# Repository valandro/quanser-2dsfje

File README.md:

# quanser-2dsfje

## Limit sensors schematic

## Authors

- Lucas Valandro (@valandro)
- Lucas Tansini (@lucastansini)
- Gustavo Francisco (@guga581)

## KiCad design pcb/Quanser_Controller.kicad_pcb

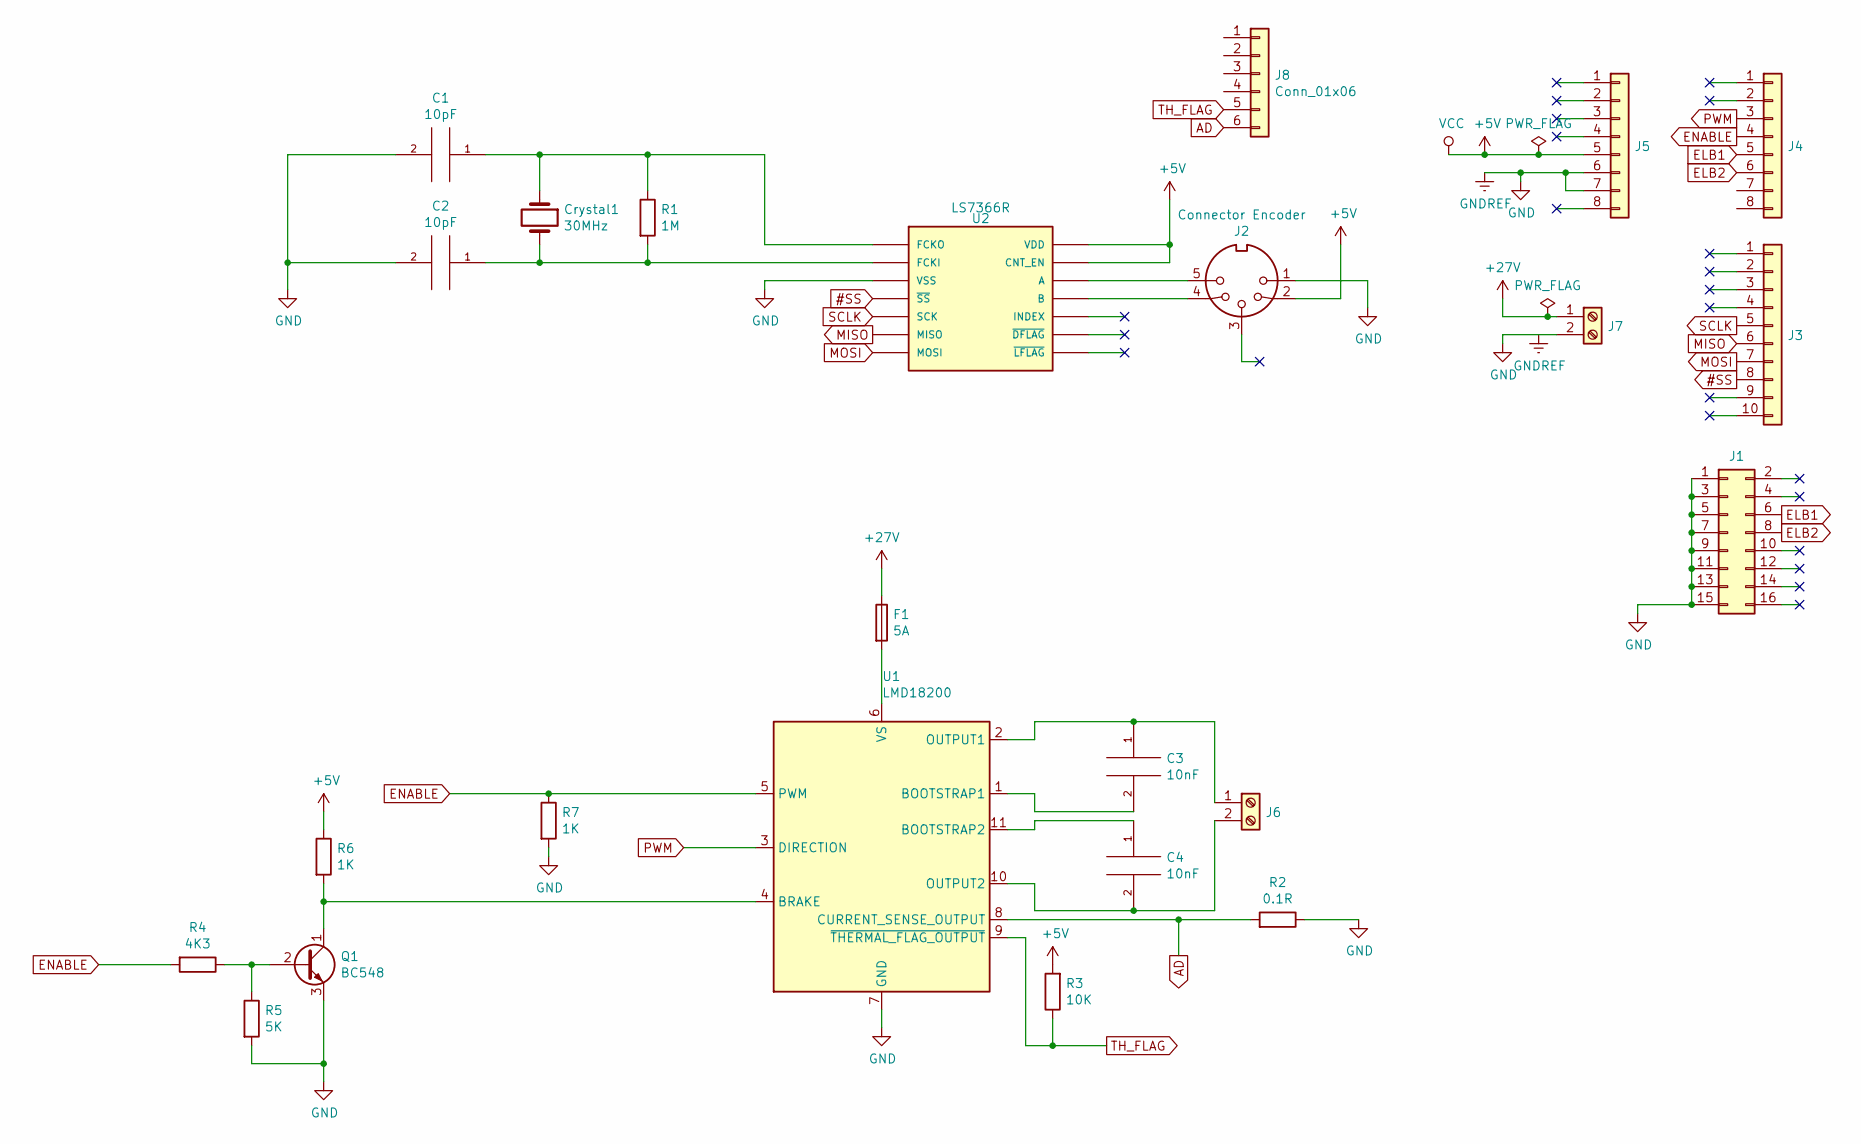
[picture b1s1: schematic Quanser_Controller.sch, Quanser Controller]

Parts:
C1, C2: 10pF; C_Disc_D3.0mm_W2.0mm_P2.50mm
C3, C4: 10nF; C_Disc_D3.0mm_W2.0mm_P2.50mm
Crystal1: 30MHz; Crystal_HC52-6mm_Vertical
F1: 5A; Fuseholder_Cylinder-5x20mm_Schurter_0031_8201_Horizontal_Op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
J1: Conn_02x08; PinHeader_2x08_P2.00mm_Vertical
J2: Connector Encoder; PinHeader_1x05_P2.54mm_Vertical
J3: Conn_01x10; PinHeader_1x10_P2.00mm_Vertical
J4, J5: Conn_01x08; PinHeader_1x08_P2.00mm_Vertical
J6, J7: Screw_Terminal_01x02; TerminalBlock_Altech_AK300-2_P5.00mm
J8: Conn_01x06; PinHeader_1x06_P2.00mm_Vertical
Q1: BC548; TO-92_Inline
R1: 1M; R_Axial_DIN0204_L3.6mm_D1.6mm_P5.08mm_Horizontal
R2: 0.1R; R_Axial_DIN0204_L3.6mm_D1.6mm_P5.08mm_Horizontal
R3: 10K; R_Axial_DIN0204_L3.6mm_D1.6mm_P5.08mm_Horizontal
R4: 4K3; R_Axial_DIN0204_L3.6mm_D1.6mm_P5.08mm_Horizontal
R5: 5K; R_Axial_DIN0204_L3.6mm_D1.6mm_P5.08mm_Horizontal
R6, R7: 1K; R_Axial_DIN0204_L3.6mm_D1.6mm_P5.08mm_Horizontal
U1: LMD18200; TO-220-11_P3.4x5.08mm_StaggerOdd_Lead4.85mm_Vertical
U2: LS7366R; DIP-14_W7.62mm

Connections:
#SS: J3.8, U2.4 (~SS~)
+5V: J2.2, J5.5, R3.2, R6.1, U2.13 (CNT_EN), U2.14 (VDD)
+28V: F1.1, J7.1
AD: J8.6, R2.2, U1.8 (CURRENT_SENSE_OUTPUT)
ELB1: J1.6, J4.5
ELB2: J1.8, J4.6
ENABLE: J4.4, R4.2, R7.1, U1.5 (PWM)
GND: C1.2, C2.2, J1.1, J1.3, J1.5, J1.7, J1.9, J1.11, J1.13, J1.15, J2.1, J5.6, J5.7, J7.2, Q1.3 (E), R2.1, R5.2, R7.2, U1.7 (GND), U2.3 (VSS)
MISO: J3.6, U2.6 (MISO)
MOSI: J3.7, U2.7 (MOSI)
unnamed: C1.1, Crystal1.1, R1.1, U2.1 (FCKO)
unnamed: C2.1, Crystal1.2, R1.2, U2.2 (FCKI)
unnamed: C3.1, J6.1, U1.2 (OUTPUT1)
unnamed: C3.2, U1.1 (BOOTSTRAP1)
unnamed: C4.1, U1.11 (BOOTSTRAP2)
unnamed: C4.2, J6.2, U1.10 (OUTPUT2)
unnamed: F1.2, U1.6 (VS)
unnamed: J2.4, U2.11 (B)
unnamed: J2.5, U2.12 (A)
unnamed: Q1.1 (C), R6.2, U1.4 (BRAKE)
unnamed: Q1.2 (B), R4.1, R5.1
PWM: J4.3, U1.3 (DIRECTION)
SCLK: J3.5, U2.5 (SCK)
TH_FLAG: J8.5, R3.1, U1.9 (~THERMAL_FLAG_OUTPUT)

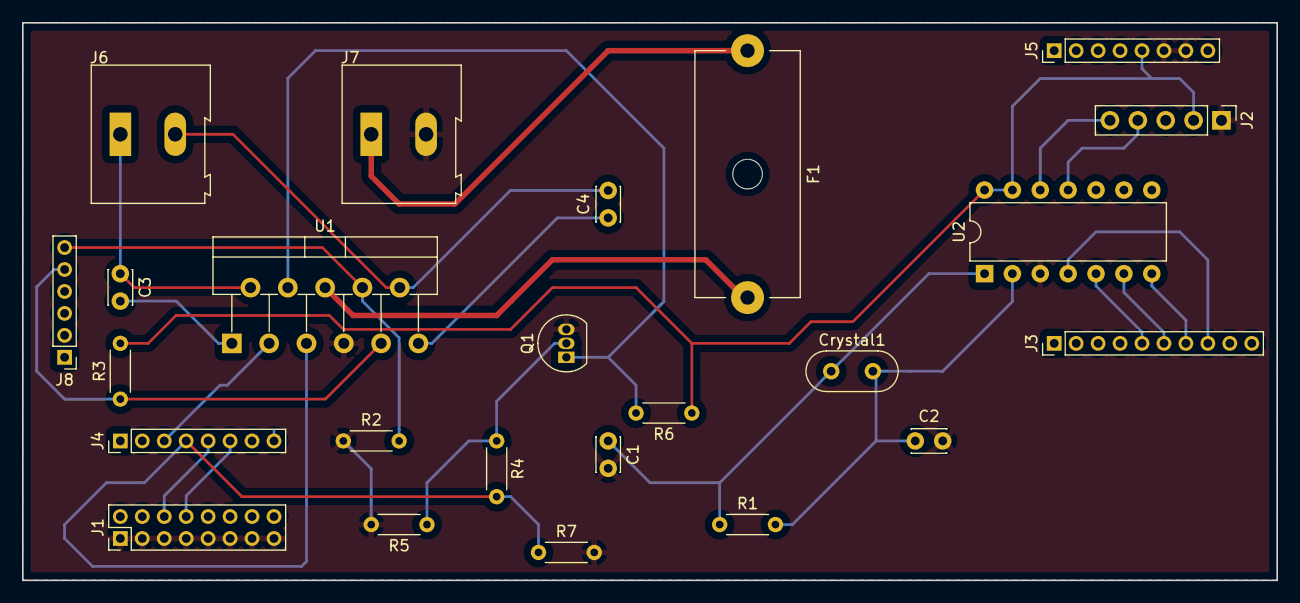
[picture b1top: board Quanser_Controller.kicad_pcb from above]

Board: 2 copper layers, 114.3 x 50.8 mm, 24 parts (0 on the bottom side), 24 nets.

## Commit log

2020-07-14 [KICAD] Limit sensors schematic.
2020-07-14 Remove .DS_Store.
2020-07-15 Fixing labels placement in Windows
2020-07-15 [KICAD] Remove SNAPSHOT project.
2020-08-01 Add initial structure to API.
2020-08-02 Add end of course sensors function.
2020-08-04 [DOXYGEN] Added documentation
    - Updated .gitignore for Doxygen generation output folder located at src/documentation/generatedDocumentation/;
    - Added template documentation for Doxygen;
    - Running command is "make documentation-example"
2020-08-08 Add brigde component.
2020-08-11 Add initialization script.
2020-08-15 Update schematic.
2020-08-15 Fix motor AC to DC symbol.
2020-08-18 Add PWM and ENABLE logic to brake the motor.
2020-08-18 add library
2020-08-18 Fix unconnected pins.
2020-08-18 update pcb; add netlist
2020-08-19 Update the project.
2020-08-20 Add NOT port to project.
2020-08-20 Update NOT port.
2020-08-23 Add netlist.
2020-08-23 Remove footprint.
2020-08-23 new library
2020-08-23 Update footprint.
2020-08-23 3d viewer
2020-08-23 Add Gerber files.
2020-08-26 Ajusta esquemático.
2020-08-30 Update project.
2020-09-02 update pcb
2020-09-02 new gerbers and drill
2020-09-02 Adjust schematic.
2020-09-03 Added initial PID Controller "class"
2020-09-03 update PCB; included reports; add A/D
2020-09-04 Add PWM init/stop and script configuration.
2020-09-05 Last update PCB
2020-09-05 End of course tests.
2020-09-05 included H-Bridge
2020-09-05 Add first PWM test.
2020-09-05 BOM included
2020-09-05 Added SPI and initialize function
2020-09-05 Add PWM tests.
2020-09-05 Decoder init
2020-09-05 Fix compilation errors.
2020-09-06 Added decoder reader counter
    Added index correction and documentation for counter reader
2020-09-06 Enhancements on documentation
2020-09-06 Added doxygen for project files
2020-09-06 update doxygen
2020-09-06 update width track
2020-09-06 Modified pwm init call order, added enable/disable in h_bridge
2020-09-06 Fixed .c initial header files include
2020-09-06 Fixed read_spi and added h_bridge to makefile
2020-09-06 Added makefile
2020-09-06 Added H Bridge PWM duty cycle
2020-09-06 Added decoder function to return joint position in rads
2020-09-06 Moved PID functions
2020-09-06 Added pid controller function
2020-09-06 Added PID Test that unify all code
2020-09-06 Fix pid_test compilation errors.
2020-09-07 End PID test
2020-09-07 H brigde tests.
2020-09-07 Added in PID set desired value function and PID Unitary test
2020-09-07 fix pid controller
2020-09-07 Remove object files.
2020-09-07 Add scripts for compile and clean everthing.
2020-09-07 Remove .zip file.
2020-09-07 Fix makefile.
2020-09-07 Adjust scripts.
2020-09-07 generate rigth Gerbers
2020-09-07 update project

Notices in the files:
README.md:
License: MIT
